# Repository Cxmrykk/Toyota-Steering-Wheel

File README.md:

<div align="center">
  <h1>Toyota Steering Wheel</h1>
  <p>Toyota (20-24) EV Steering Wheel Transceiver, Clockspring and Spline Adapter.</p>
  <p>Personal project for extending compatibility with my 2003 Toyota Corolla, including extended functionality for the buttons, paddles and horn</p>
</div>

### Photos

#### Car PCB v1.0
- Molex connector for hard-wired button outputs, horn relay and interior light input
- AUX cable socket for communication with head unit (remote buttons)
- Crimp compatible power terminals

#### Car PCB v1.1
- Added digital potentiometer to replace PWM based solution for setting AUX resistance values (didn't work)

#### Car PCB v1.2
- Modified board design for more I/O accessibility
- Replaced 24 pin Molex connector with 8 screw output terminals
- Added horn relay

#### Steering Wheel PCB v1.0
- IDC connector hard-wired to existing connector wires, includes 12V power in, horn switch and GND

#### Steering Wheel PCB v1.1
- Fixed resistor ladder design (mode and CC minus buttons being same value)
- Relocated microcontroller for better USB-C accessibility

#### Clockspring Front

#### Clockspring Back

#### Spline Adapter and washer

#### Clockspring and spline adapter test fitting
- Successful fitment with SLA printed steel spline adapter and FDM printed clockspring (prototype)

### Material List

**Crimps**

- FDD1.25-250 (Horn Tab)
- RV1.25-4 (Ground)
- MDD1.25-187 and FDD1.25-187 (Power Connection)

**Screws**

- M5x12mm Flat Head Nut & Bolt

**Splicing**

- 2.5 - 3mm Diameter Heat Shrink
- Solder, and Soldering Iron
- Wire Strippers and/or Wire Cutters

**Connectors**

- 24 pin ATX cable (24-pin Molex Mini-Fit Jr.™)
- 16 pin IDC cable
- Also for the PCBs:
  - Sparkfun ATX Power Supply Connector - Right Angle (`PRT-09498`)
  - Two 7x1 Pin Headers (Female and Male) or just cut to size

**Airbag Connector**

- Typically the airbag inflator on the new steering wheel will use 1 or 2 connectors based on the 3 variations of the **AK2 Squib Connector**.
  - In my case, the Toyota EV steering wheel airbag inflator used a single **Code 2 (Blue/Green) AK2 Squib Connector**.
  - You can find each individual connector here: [Link to Molex PDF](https://www.content.molex.com/dxdam/literature/987650-4993.pdf)
- You can source these connectors either by:
  - Buying the same clockspring used with the new steering wheel (Toyota)
  - Buying a third party clockspring from older cars that happen to use the same connector (Kia, Hyundai, GM in some cases).

**Microcontrollers**

- **Xiao ESP32-C3** - Mounted inside the steering wheel
- **Xiao ESP32-S3** - Mounted in the car, below the clockspring

**Custom PCBs**

- Ordered on JLCPCB
- Please take a look in the [hardware](/hardware) directory:
  - Steering Wheel Transciever
  - Car Transciever

**Spline Adapter**

- Required to fit the steering wheel on older cars (tested working with 2003 Toyota Corolla).
- Ordered on IN3DTEC (Maraging Steel, Bead blasted)

**Clockspring**

- Provides wiring for the airbag and repurposed horn cable (12V Power)
- Printed locally using Bambu P1S (White ABS, 0.2mm nozzle)
- You must also purchase the clockspring used with the old steering wheel, as the new clockspring will reuse the spiral ribbon cable and connectors (part number: `84306-0D021`)

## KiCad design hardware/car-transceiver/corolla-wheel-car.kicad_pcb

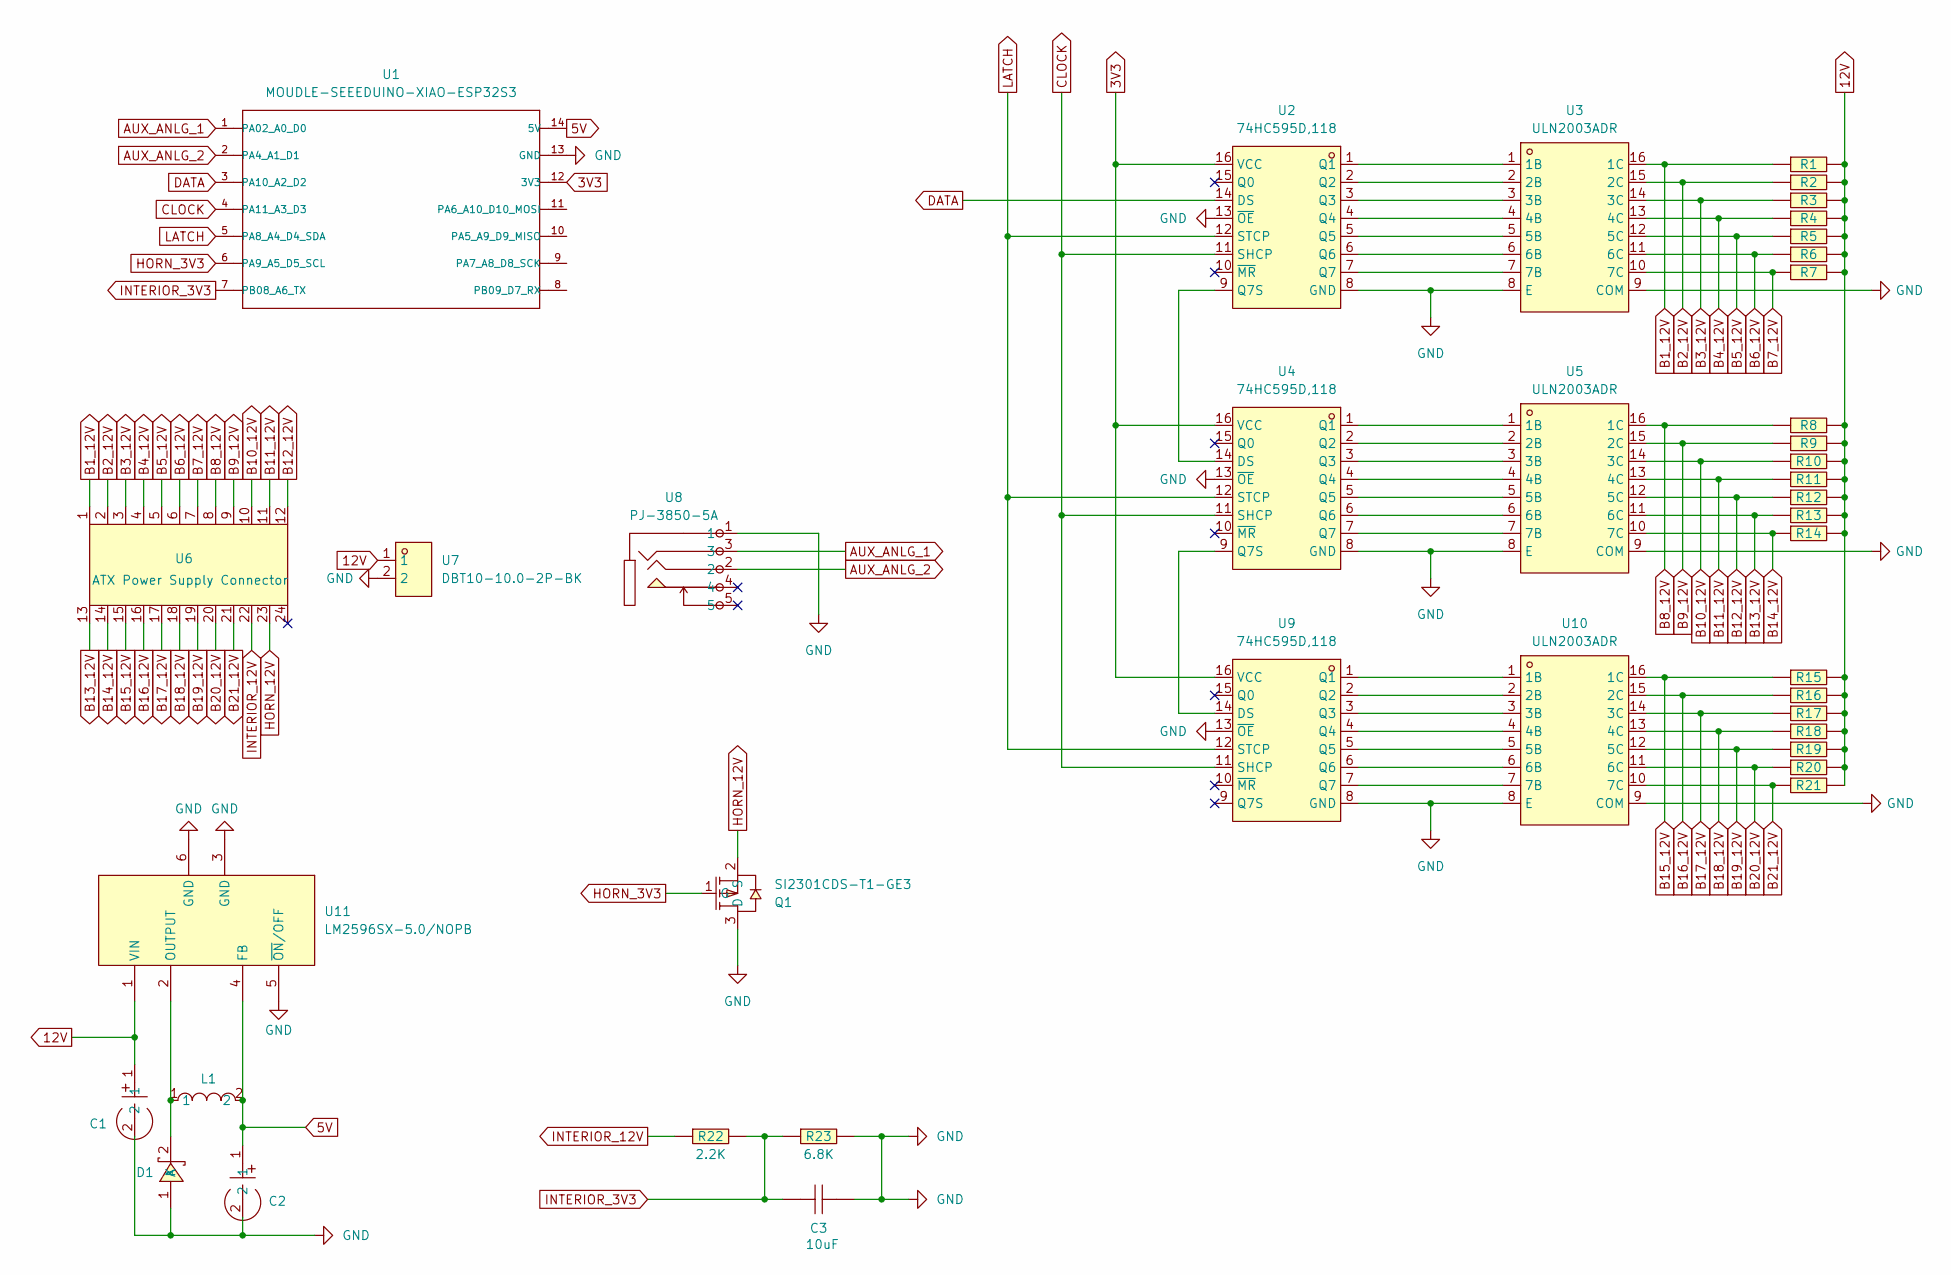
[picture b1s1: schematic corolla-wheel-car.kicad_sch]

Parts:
C1, C2: GVT1V227M0810CNVC; CAP-SMD_BD8.0-L8.3-W8.3-FD; LCSC Part C2983323
C3: 10uF; C0603; LCSC Part C96446
D1: SS54_C22452; SMA_L4.4-W2.8-LS5.4-R-RD; LCSC Part C22452
L1: NBMC1045N-101M; IND-SMD_L10.3-W10.3_1274AS-H-330M; LCSC Part C2875675
Q1: SI2301CDS-T1-GE3; SOT-23-3_L3.0-W1.7-P0.95-LS2.9-BR; LCSC Part C10487
R1, R2, R3, R4, R5, R6, R7, R8, R9, R10, R11, R12, R13, R14, R15, R16, R17, R18, R19, R20, R21: 0603WAF1001T5E; R0603; LCSC Part C21190
R22: 2.2K; R0603; LCSC Part C4190
R23: 6.8K; R0603; LCSC Part C23212
U1: MOUDLE-SEEEDUINO-XIAO-ESP32S3; XIAO-ESP32-S3-MOUNT
U2, U4, U9: 74HC595D,118; SOIC-16_L9.9-W3.9-P1.27-LS6.0-BL; LCSC Part C5947
U3, U5, U10: ULN2003ADR; SOIC-16_L9.9-W3.9-P1.27-LS6.0-BL; LCSC Part C7512
U6: ATX Power Supply Connector; ATX-Sparkfun
U7: DBT10-10.0-2P-BK; CONN-TH_2P-P10.00_DBT10-10.0-2P-BK; LCSC Part C2997277
U8: PJ-3850-5A; AUDIO-TH_PJ-3850-5A; LCSC Part C707255
U11: LM2596SX-5.0/NOPB; TO-263-5_L10.2-W8.9-P1.70-TL; LCSC Part C10002

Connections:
3V3: U1.12 (3V3), U2.16 (VCC), U4.16 (VCC), U9.16 (VCC)
5V: C2.1, L1.2, U1.14 (5V), U11.4 (FB)
12V: C1.1, R1.2, R2.2, R3.2, R4.2, R5.2, R6.2, R7.2, R8.2, R9.2, R10.2, R11.2, R12.2, R13.2, R14.2, R15.2, R16.2, R17.2, R18.2, R19.2, R20.2, R21.2, U7.1, U11.1 (VIN)
AUX_ANLG_1: U1.1 (PA02_A0_D0), U8.3
AUX_ANLG_2: U1.2 (PA4_A1_D1), U8.2
B1_12V: R1.1, U3.16 (1C), U6.1
B2_12V: R2.1, U3.15 (2C), U6.2
B3_12V: R3.1, U3.14 (3C), U6.3
B4_12V: R4.1, U3.13 (4C), U6.4
B5_12V: R5.1, U3.12 (5C), U6.5
B6_12V: R6.1, U3.11 (6C), U6.6
B7_12V: R7.1, U3.10 (7C), U6.7
B8_12V: R8.1, U5.16 (1C), U6.8
B9_12V: R9.1, U5.15 (2C), U6.9
B10_12V: R10.1, U5.14 (3C), U6.10
B11_12V: R11.1, U5.13 (4C), U6.11
B12_12V: R12.1, U5.12 (5C), U6.12
B13_12V: R13.1, U5.11 (6C), U6.13
B14_12V: R14.1, U5.10 (7C), U6.14
B15_12V: R15.1, U6.15, U10.16 (1C)
B16_12V: R16.1, U6.16, U10.15 (2C)
B17_12V: R17.1, U6.17, U10.14 (3C)
B18_12V: R18.1, U6.18, U10.13 (4C)
B19_12V: R19.1, U6.19, U10.12 (5C)
B20_12V: R20.1, U6.20, U10.11 (6C)
B21_12V: R21.1, U6.21, U10.10 (7C)
CLOCK: U1.4 (PA11_A3_D3), U2.11 (SHCP), U4.11 (SHCP), U9.11 (SHCP)
DATA: U1.3 (PA10_A2_D2), U2.14 (DS)
GND: C1.2, C2.2, C3.2, D1.1 (A), Q1.3 (D), R23.2, U1.13 (GND), U2.8 (GND), U2.13 (~OE), U3.8 (E), U3.9 (COM), U4.8 (GND), U4.13 (~OE), U5.8 (E), U5.9 (COM), U7.2, U8.1, U9.8 (GND), U9.13 (~OE), U10.8 (E), U10.9 (COM), U11.3 (GND), U11.5 (~ON/OFF), U11.6 (GND)
HORN_3V3: Q1.1 (G), U1.6 (PA9_A5_D5_SCL)
HORN_12V: Q1.2 (S), U6.23
INTERIOR_3V3: C3.1, R22.2, R23.1, U1.7 (PB08_A6_TX)
INTERIOR_12V: R22.1, U6.22
LATCH: U1.5 (PA8_A4_D4_SDA), U2.12 (STCP), U4.12 (STCP), U9.12 (STCP)
unnamed: D1.2 (K), L1.1, U11.2 (OUTPUT)
unnamed: U2.1 (Q1), U3.1 (1B)
unnamed: U2.2 (Q2), U3.2 (2B)
unnamed: U2.3 (Q3), U3.3 (3B)
unnamed: U2.4 (Q4), U3.4 (4B)
unnamed: U2.5 (Q5), U3.5 (5B)
unnamed: U2.6 (Q6), U3.6 (6B)
unnamed: U2.7 (Q7), U3.7 (7B)
unnamed: U2.9 (Q7S), U4.14 (DS)
unnamed: U4.1 (Q1), U5.1 (1B)
unnamed: U4.2 (Q2), U5.2 (2B)
unnamed: U4.3 (Q3), U5.3 (3B)
unnamed: U4.4 (Q4), U5.4 (4B)
unnamed: U4.5 (Q5), U5.5 (5B)
unnamed: U4.6 (Q6), U5.6 (6B)
unnamed: U4.7 (Q7), U5.7 (7B)
unnamed: U4.9 (Q7S), U9.14 (DS)
unnamed: U9.1 (Q1), U10.1 (1B)
unnamed: U9.2 (Q2), U10.2 (2B)
unnamed: U9.3 (Q3), U10.3 (3B)
unnamed: U9.4 (Q4), U10.4 (4B)
unnamed: U9.5 (Q5), U10.5 (5B)
unnamed: U9.6 (Q6), U10.6 (6B)
unnamed: U9.7 (Q7), U10.7 (7B)

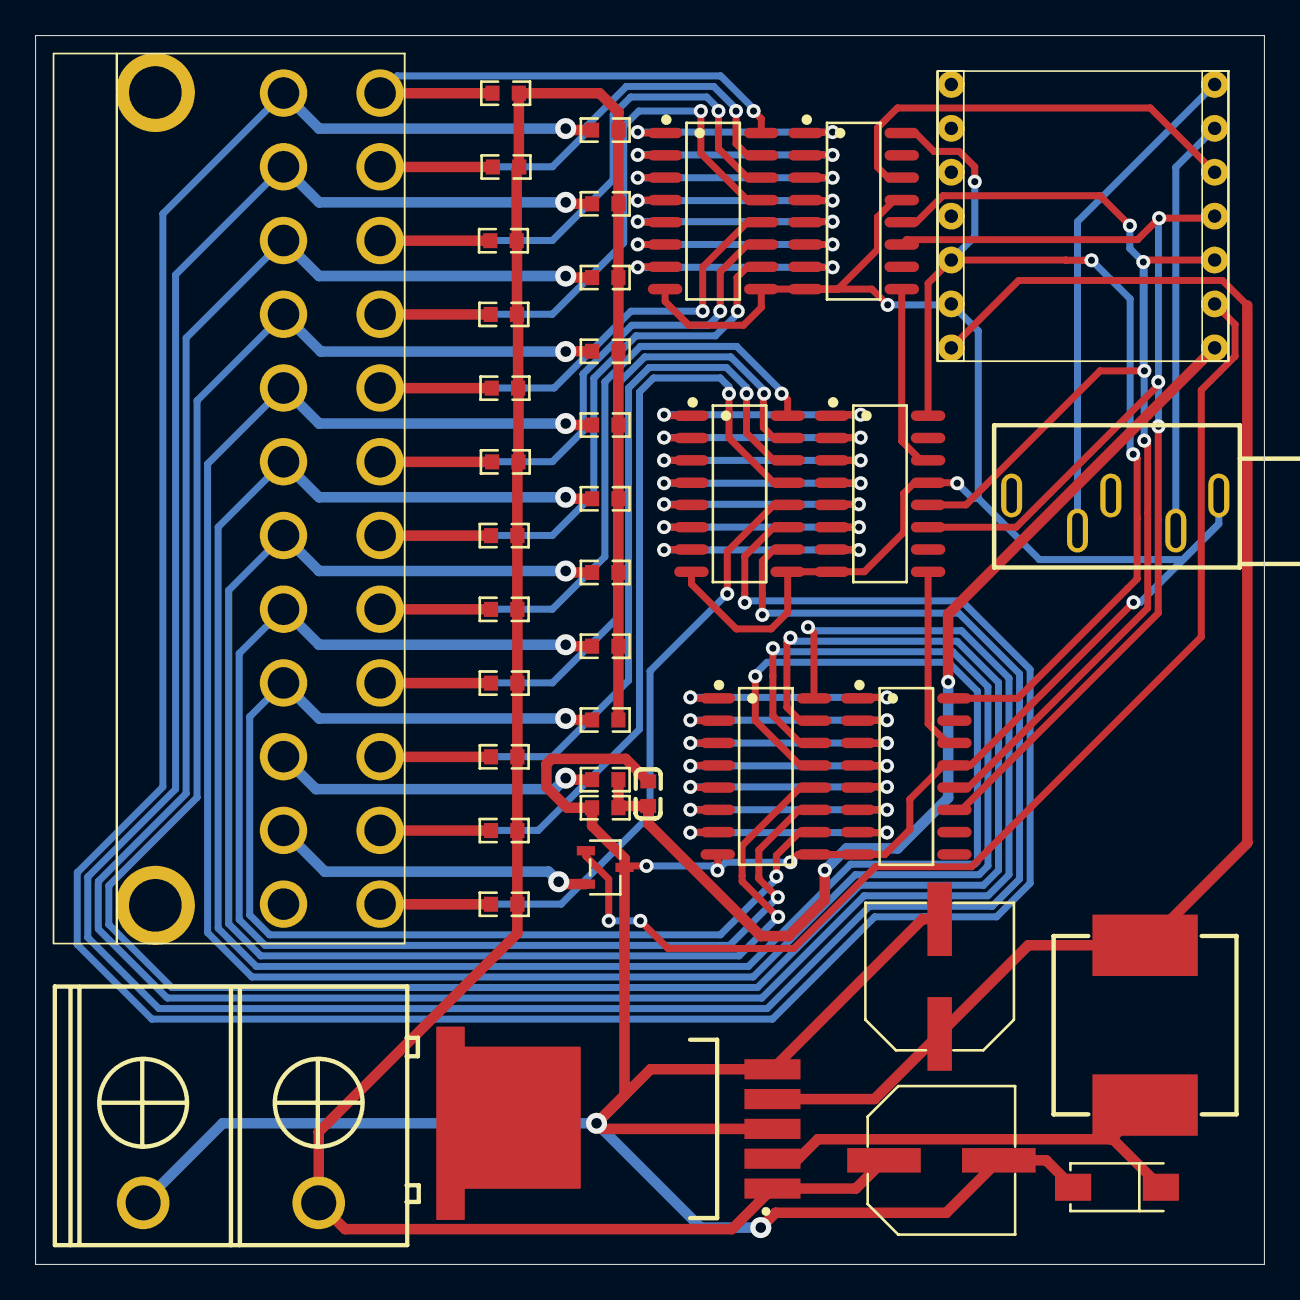
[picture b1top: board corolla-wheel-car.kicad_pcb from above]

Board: 2 copper layers, 70.0 x 70.0 mm, 40 parts (0 on the bottom side), 58 nets.

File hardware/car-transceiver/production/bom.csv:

Designator,Footprint,Quantity,Value,LCSC Part #
"C1, C2",CAP-SMD_BD8.0-L8.3-W8.3-FD,2,GVT1V227M0810CNVC,
C3,C0603,1,10uF,
D1,SMA_L4.4-W2.8-LS5.4-R-RD,1,SS54_C22452,
L1,IND-SMD_L10.3-W10.3_1274AS-H-330M,1,NBMC1045N-101M,
Q1,SOT-23-3_L3.0-W1.7-P0.95-LS2.9-BR,1,SI2301CDS-T1-GE3,
"R1, R10, R11, R12, R13, R14, R15, R16, R17, R18, R19, R2, R20, R21, R3, R4, R5, R6, R7, R8, R9",R0603,21,0603WAF1001T5E,
R22,R0603,1,2.2K,
R23,R0603,1,6.8K,
U1,XIAO-ESP32-S3-MOUNT,1,MOUDLE-SEEEDUINO-XIAO-ESP32S3,
"U10, U3, U5",SOIC-16_L9.9-W3.9-P1.27-LS6.0-BL,3,ULN2003ADR,
U11,TO-263-5_L10.2-W8.9-P1.70-TL,1,LM2596SX-5.0/NOPB,
"U2, U4, U9",SOIC-16_L9.9-W3.9-P1.27-LS6.0-BL,3,"74HC595D,118",
U6,ATX-Sparkfun,1,ATX Power Supply Connector,
U7,CONN-TH_2P-P10.00_DBT10-10.0-2P-BK,1,DBT10-10.0-2P-BK,
U8,AUDIO-TH_PJ-3850-5A,1,PJ-3850-5A,

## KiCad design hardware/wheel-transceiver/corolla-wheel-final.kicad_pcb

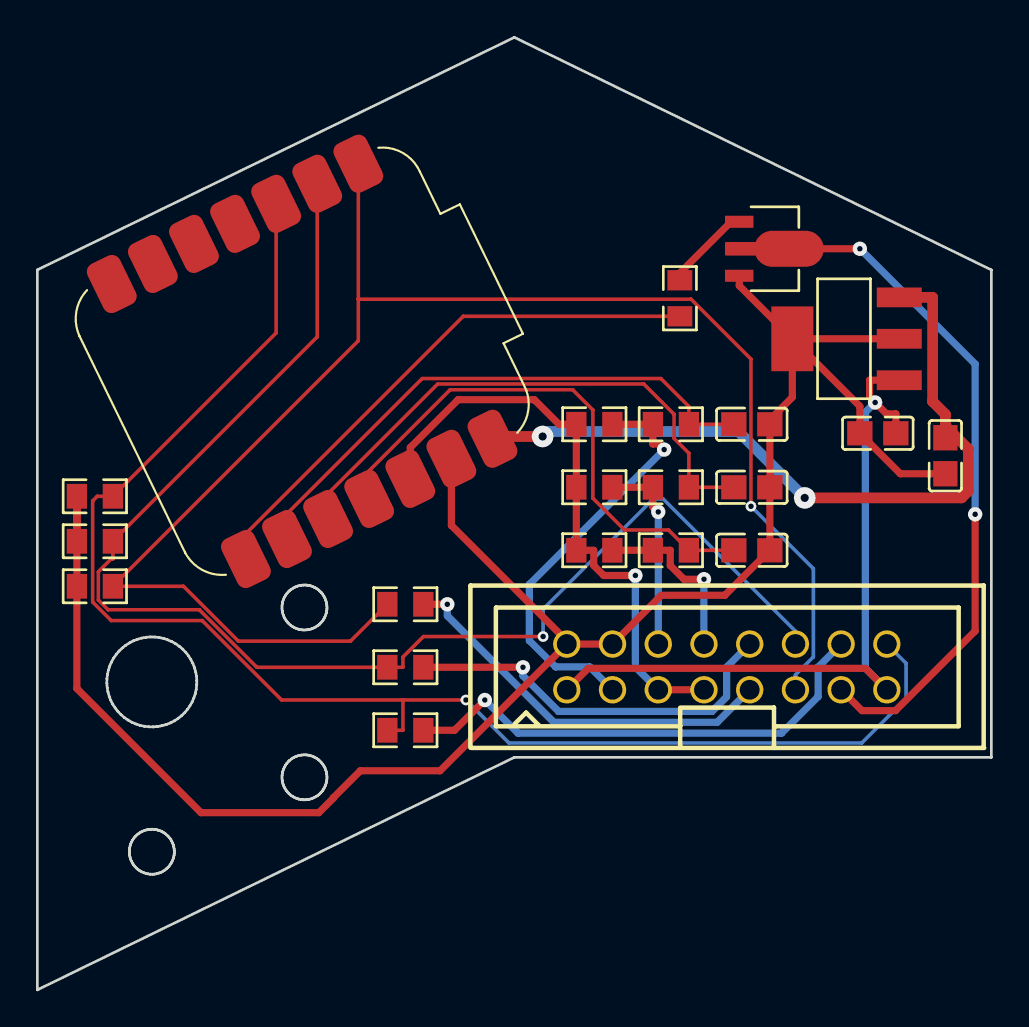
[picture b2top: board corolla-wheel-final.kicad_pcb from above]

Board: 2 copper layers, 53.0 x 52.9 mm, 22 parts (0 on the bottom side), 19 nets.

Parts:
C1, C2, C3, C4, C5: 10uF; C0805
P1: HDR-IDC-2.54-2X8P; IDC-TH_16P-P2.54_C3406
Q1: D882_C9634; SOT-89-3_L4.5-W2.5-P1.50-LS4.2-BR
R1, R2, R7, R8, R11, R12, R13: 1K; R0805
R3, R5: 680; R0805
R4, R6, R10: 330; R0805
R9: 1.5K; R0805
U2: MOUDLE-SEEEDUINO-XIAO-ESP32C3; MCU_Seeed_ESP32C3
U5: LM2940S-5.0; SOT-223-3_L6.5-W3.4-P2.30-LS7.0-BR

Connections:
3V3: P1.5, P1.7, R1.2, R7.2, R12.2, U2.12 (3V3)
5V: C3.1, U2.14 (5V), U5.3 (VOUT)
A0: P1.11, R3.1, R4.2, U2.1 (PA02_A0_D0)
A1: P1.12, R5.1, R6.2, U2.2 (PA4_A1_D1)
A2: P1.16, R9.1, R10.2, U2.3 (PA10_A2_D2)
BATT: C1.2, P1.1, P1.15, U5.1 (VIN)
BROWN: P1.9, R3.2
D7: R11.2, U2.8 (PB09_A7_D7_RX)
D8: C5.1, R13.1, U2.9 (PA7_A8_D8_SCK)
D9: C4.1, R8.1, U2.10 (PA5_A9_D9_MISO)
D10: C2.1, R2.1, U2.11 (PA6_A10_D10_MOSI)
GND: C1.1, C2.2, C3.2, C4.2, C5.2, P1.2, P1.4, Q1.3 (E), R4.1, R6.1, R10.1, U2.13 (GND), U5.2 (GND), U5.4 (GND)
GRAY: P1.14, R9.2
HORN: P1.3, R12.1, R13.2
unnamed: Q1.1 (B), R11.1
ORANGE: P1.10, R5.2
PADDLE_LEFT: P1.8, R1.1, R2.2
PADDLE_RIGHT: P1.6, R7.1, R8.2
WHITE-BLACK: P1.13, Q1.2 (C)

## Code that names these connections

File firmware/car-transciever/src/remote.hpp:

#pragma once

#include <Arduino.h>
#include <map>

// PWM Configuration
#define PIN_LATCH D2

struct PWMConfig {
  uint16_t value;
};

enum class ButtonID : uint8_t {
  NONE = 0,
  MODE = 1,
  LEFT = 2,
  NEXT_SONG = 3,
  OK = 4,
  UP = 5,
  PREV_SONG = 6,
  RETURN = 7,
  PHONE = 8,
  DOWN = 9,
  VOLUME_UP = 10,
  ASSISTANT = 11,
  RIGHT = 12,
  VOLUME_DOWN = 13,
  CRUISE_CONTROL = 14,
  CANCEL = 15,
  CC_PLUS = 16,
  CC_MINUS = 17,
  RADAR = 18,
  LANE_ASSIST = 19,
  PADDLE_LEFT = 20,
  PADDLE_RIGHT = 21,
  HORN = 22,
  BACKLIGHT = 23,  // Receive only
};

// Map ButtonID to PWM configuration
const std::map<ButtonID, uint8_t> BUTTON_SPI_MAP = {
    // Volume controls on AUX_1
    {ButtonID::VOLUME_UP, 255},
    {ButtonID::VOLUME_DOWN, 255 - 1},

    // Media controls on AUX_1
    {ButtonID::NEXT_SONG, 255 - 2},
    {ButtonID::PREV_SONG, 255 - 3},

    // Phone controls on AUX_2
    {ButtonID::PHONE, 255 - 4},
    {ButtonID::RETURN, 255 - 5},

    // Navigation controls on AUX_2
    {ButtonID::ASSISTANT, 255 - 6},
    {ButtonID::MODE, 255 - 7},
};

// Function to set PWM output for a button
inline void setRemoteState(ButtonID button, bool isPressed) {
  auto it = BUTTON_SPI_MAP.find(button);
  if (it != BUTTON_SPI_MAP.end()) {
    Serial.println(static_cast<int>(button));

    // Pull latch pin low to start transfer
    digitalWrite(PIN_LATCH, LOW);

    // Transfer data for each register
    SPI.transfer(isPressed ? it->second : 0);

    // Pull latch pin high to update outputs
    digitalWrite(PIN_LATCH, HIGH);
  }
}

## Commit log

2024-09-12 Add spline OpenSCAD drawings
2024-09-12 Add transceiver schematics
2024-09-12 Remove cache files
2024-09-12 Add README.md
2024-09-12 Add steering wheel button schematics
2024-10-09 Add clockspring files
2024-10-09 Modify README.md
2024-11-24 Update progress
2024-11-24 Change README.md
2024-11-24 Add new hardware files
2024-11-24 Add parts
2024-11-24 Add button testing firmware
2024-11-24 Add ON/OFF logic
2024-11-24 Adjust threshold values
2024-11-24 Double check readings
2024-11-27 Working bluetooth client
2024-11-27 Remove server debugging
2024-11-27 Remove client debugging
2024-11-27 Implement button packets
2024-11-27 Read button packets
2024-11-28 Update model
2024-12-01 Button messages working
2024-12-02 Improve BTLE reliability
2024-12-02 Communicate interior lighting state
2025-01-05 Update for wheel V2 board
2025-01-07 Add shift register support
2025-02-21 Use SPI.h for new board revision
2025-02-21 Change PWM to SPI for new components
2025-02-22 Fix digital potentiometer state
2025-03-05 Use corrected model
2025-03-05 Update README.md with assets
2025-04-05 Add clockspring part number
2025-04-05 Support V3.0 board
